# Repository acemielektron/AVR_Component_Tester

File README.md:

# AVR_Component_Tester
DIY single sided PCB for AVR Component Tester (based on pdf file by Karl-Heinz Kübbeler)

A very useful gadget whether you buy from many clones available or build it yourself. Here is my version:

pcb</img>

schematic</img>

photos of built device:
without 2x16 lcd screen</img>

screen installed and working</img>

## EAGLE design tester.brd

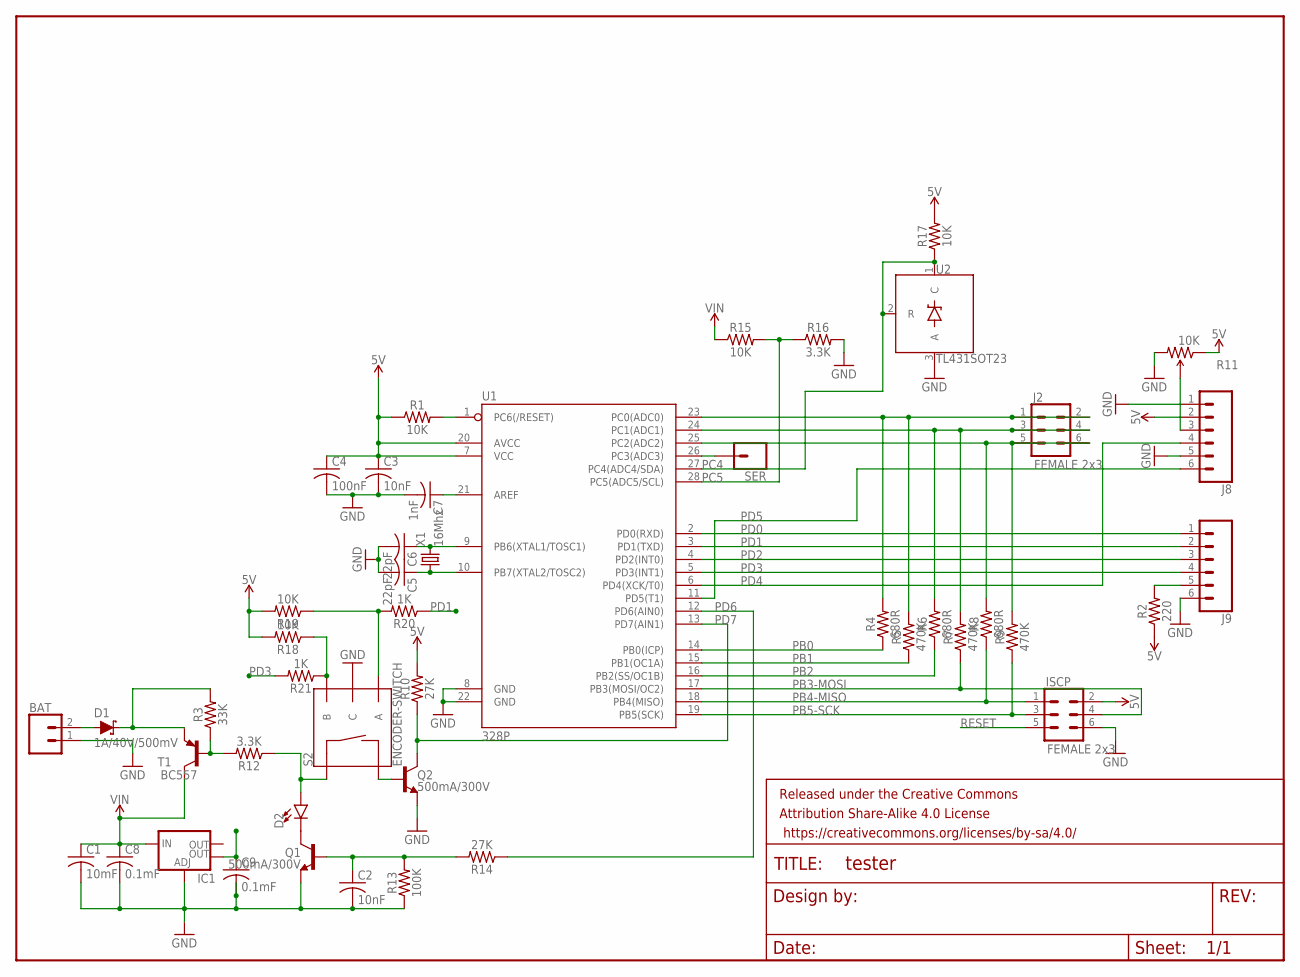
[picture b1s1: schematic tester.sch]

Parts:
BAT: CONN_02; 1X02
C1: 10mF; C0805
C2, C3: 10nF; C0805
C4: 100nF; C0805
C5, C6: 22pF; C0805
C7: 1nF; C0805
C8, C9: 0.1mF; C0805
D1: 1A/40V/500mV; SMA-DIODE
D2: LED3MM; LED_3MM
FRAME1: FRAME-LETTER; CREATIVE_COMMONS
IC1: V_REG_LM1117SOT223; SOT223
ISCP: FEMALE 2x3; 2X3
J2: FEMALE 2x3; 2X3
J8, J9: CONN_06SILK_FEMALE_PTH; 1X06
Q1, Q2: 500mA/300V; SOT23-3
R1, R17, R18, R19: 10K; 0805
R2: 220; 1206
R3: 33K; 1206
R4, R6, R8: 680R; AXIAL-0.3
R5, R7, R9: 470K; AXIAL-0.3
R10, R14: 27K; 1206
R11: 10K; TRIM_POT_PTH
R12, R16: 3.3K; 1206
R13: 100K; 0805
R15: 10K; 1206
R20, R21: 1K; 0805
S2: ENCODER-SWITCH; ROTARY_ENC_PLAIN
SER: CONN_01; 1X01
T1: BC557; TO92-EBC
U1: 328P; DIP28
U2: TL431SOT23; SOT23-3
X1: 16Mhz; HC49

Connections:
5V: C3.1, C4.1, C9.1, IC1.4 (OUT), ISCP.2, J8.2, R1.1, R2.1, R10.2, R11.1 (CCW), R17.2, R18.2, R19.2, U1.7 (VCC), U1.20 (AVCC)
GND: BAT.1, C1.2, C2.2, C3.2, C4.2, C5.2, C6.2, C7.2, C8.2, C9.2, IC1.1 (ADJ), ISCP.6, J8.1, J8.5, J9.6, Q1.2 (E), Q2.2 (E), R11.3 (CW), R13.1, R16.2, S2.C, U1.8 (GND), U1.22 (GND), U2.3 (A)
unnamed: C6.1, U1.9 (PB6(XTAL1/TOSC1)), X1.2
unnamed: C5.1, U1.10 (PB7(XTAL2/TOSC2)), X1.1
unnamed: C7.1, U1.21 (AREF)
unnamed: J9.5, R2.2
unnamed: J8.3, R11.2 (WIPER)
unnamed: D2.K (C), Q1.3 (C)
unnamed: R18.1, R21.1, S2.B
unnamed: BAT.2, D1.A
unnamed: R3.1, R12.2, T1.B
unnamed: C2.1, Q1.1 (B), R13.2, R14.2
unnamed: D1.C, R3.2, T1.E
unnamed: D2.A, R12.1, S2.SW+
unnamed: R19.1, R20.2, S2.A
unnamed: Q2.1 (B), S2.SW-
PB0: R4.P$1 (1), U1.14 (PB0(ICP))
PB1: R5.P$1 (1), U1.15 (PB1(OC1A))
PB2: R6.P$1 (1), U1.16 (PB2(SS/OC1B))
PB3-MOSI: ISCP.4, R7.P$1 (1), U1.17 (PB3(MOSI/OC2))
PB4-MISO: ISCP.1, R8.P$1 (1), U1.18 (PB4(MISO))
PB5-SCK: ISCP.3, R9.P$1 (1), U1.19 (PB5(SCK))
PC4: R17.1, U1.27 (PC4(ADC4/SDA)), U2.1 (C), U2.2 (R)
PC5: R15.2, R16.1, U1.28 (PC5(ADC5/SCL))
PD0: J9.1, U1.2 (PD0(RXD))
PD1: J9.2, R20.1, U1.3 (PD1(TXD))
PD2: J9.3, U1.4 (PD2(INT0))
PD3: J9.4, R21.2, U1.5 (PD3(INT1))
PD4: J8.4, U1.6 (PD4(XCK/T0))
PD5: J8.6, U1.11 (PD5(T1))
PD6: R14.1, U1.12 (PD6(AIN0))
PD7: Q2.3 (C), R10.1, U1.13 (PD7(AIN1))
RESET: ISCP.5, R1.2, U1.1 (PC6(/RESET))
SERIAL: SER.1, U1.26 (PC3(ADC3))
TP1: J2.1, J2.2, R4.P$2 (2), R5.P$2 (2), U1.23 (PC0(ADC0))
TP2: J2.3, J2.4, R6.P$2 (2), R7.P$2 (2), U1.24 (PC1(ADC1))
TP3: J2.5, J2.6, R8.P$2 (2), R9.P$2 (2), U1.25 (PC2(ADC2))
VIN: C1.1, C8.1, IC1.3 (IN), R15.1, T1.C

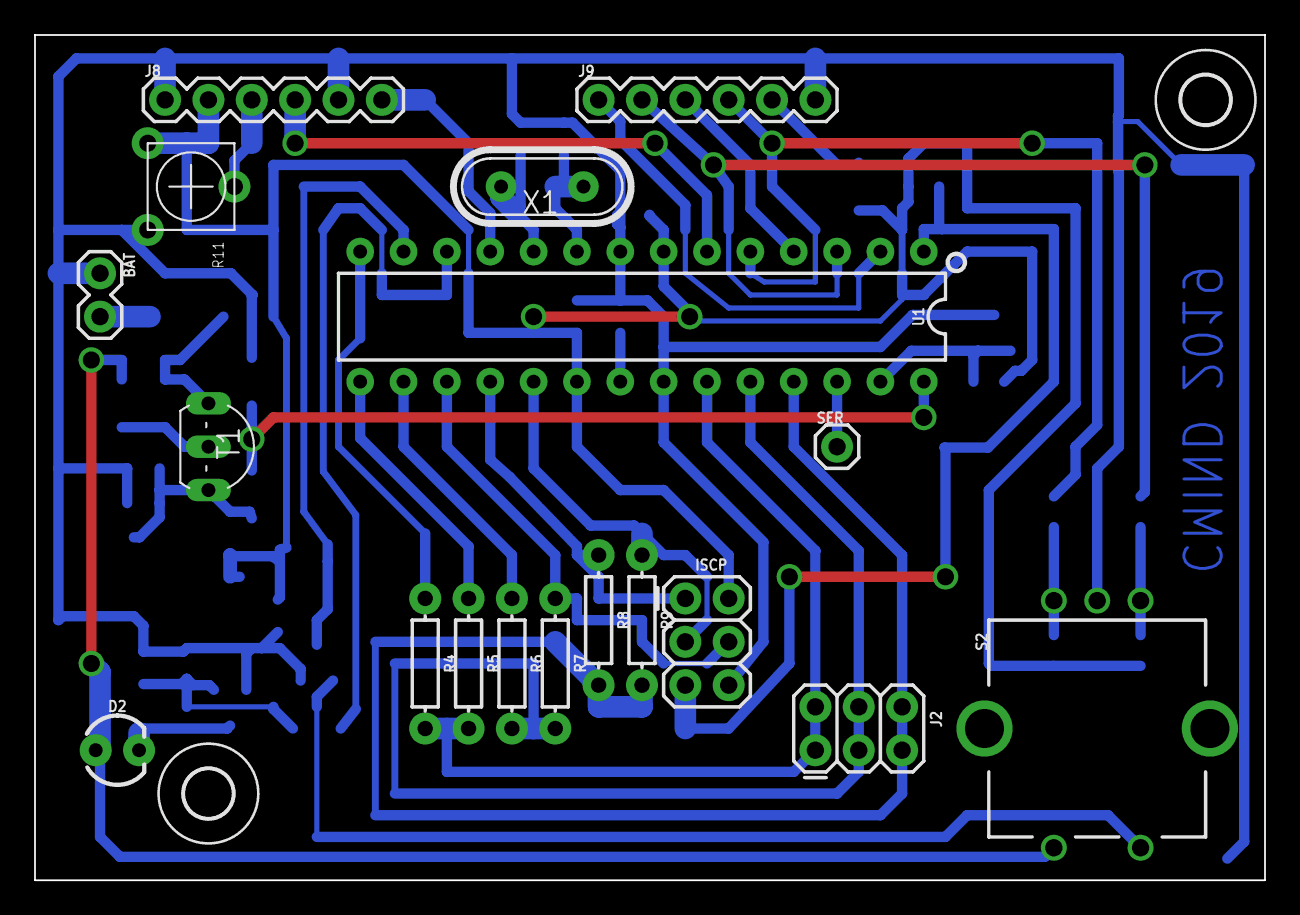
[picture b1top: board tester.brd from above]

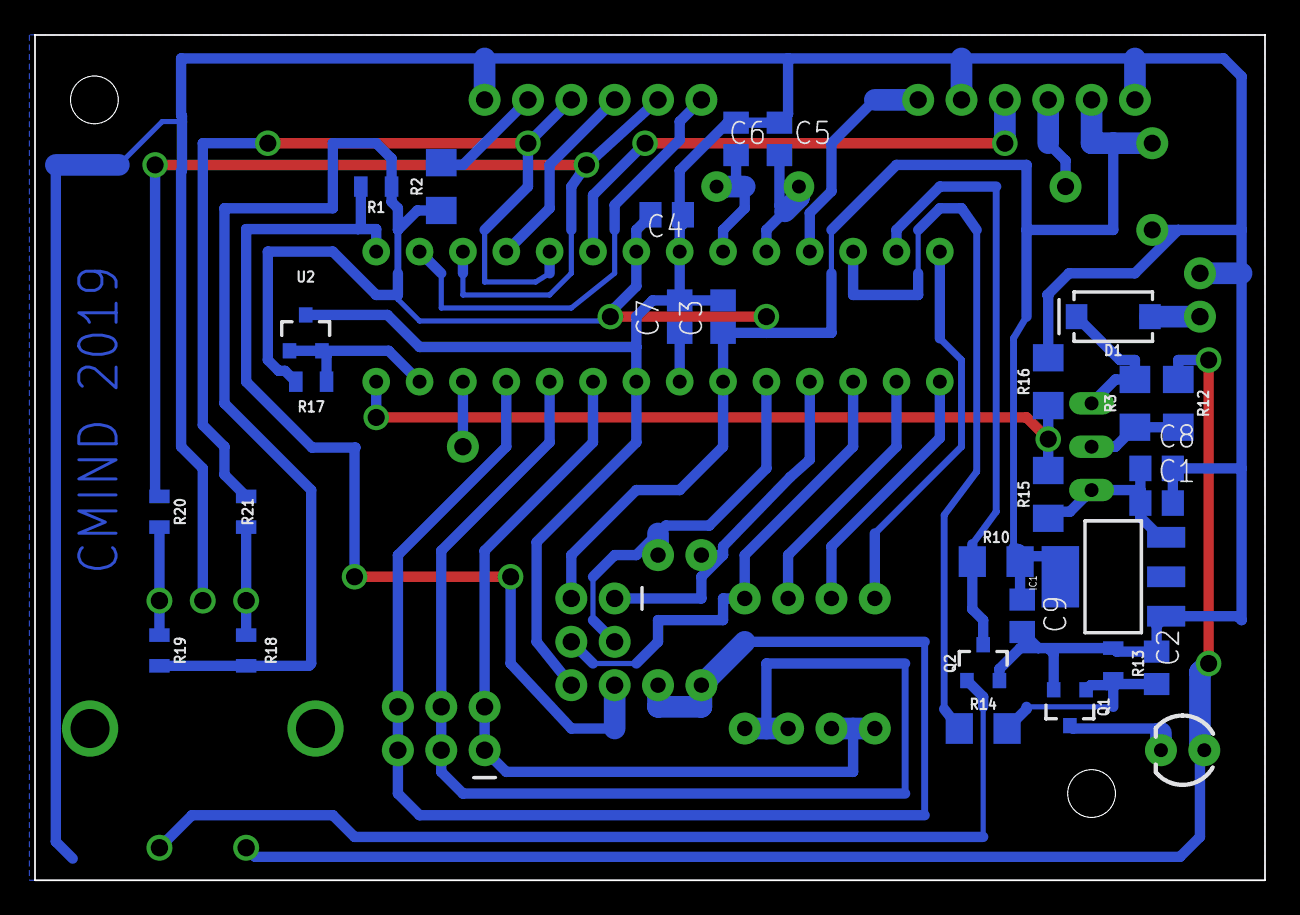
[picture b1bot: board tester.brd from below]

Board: 2 copper layers, 72.1 x 49.5 mm, 49 parts (28 on the bottom side), 38 nets.

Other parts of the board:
U$1, U$2: 2,8

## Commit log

2019-02-14 Add files via upload
    single sided mini pcb for AVR Component Tester
2019-02-14 Source pdf file by Karl-Heinz Kübbeler added for reference
2019-03-08 Photos
2019-07-24 Update & cleanup

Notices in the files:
parts and their libraries:
SparkFun-Connectors: Licensing: Creative Commons ShareAlike 4.0 International - https://creativecommons.org/licenses/by-sa/4.0
SparkFun-Aesthetics: Released under the Creative Commons Attribution Share-Alike 4.0 License
SparkFun-Aesthetics: https://creativecommons.org/licenses/by-sa/4.0
